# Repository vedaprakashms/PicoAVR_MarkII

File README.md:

# PicoAVR_MarkII
PicoAVR Mark II board redesigned based on CH552G, this project is heavily influenced by  https://github.com/vedaprakashms/AVR-Programmer/tree/master/picoAVR_Programmer

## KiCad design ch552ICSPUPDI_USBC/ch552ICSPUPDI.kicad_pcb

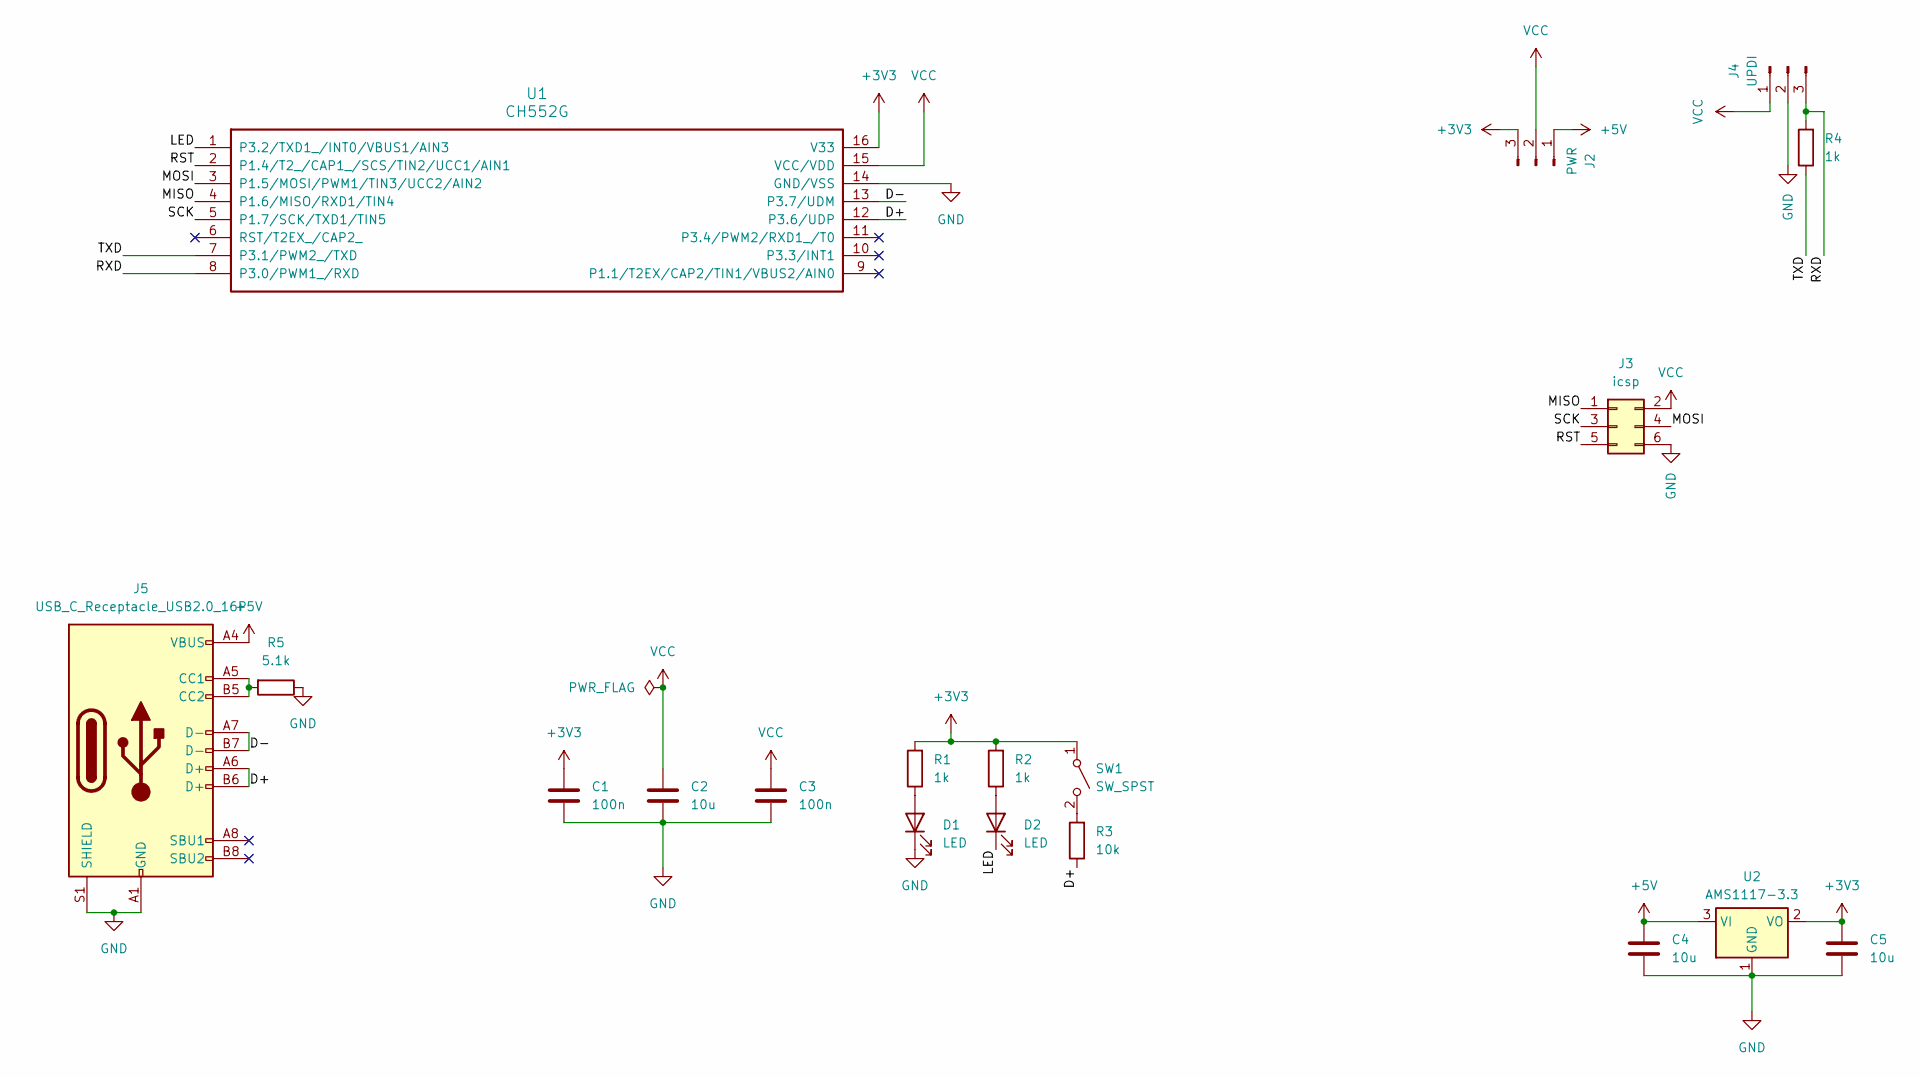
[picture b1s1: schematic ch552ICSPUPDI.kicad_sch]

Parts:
C1, C3: 100n; C_0603_1608Metric_Pad1.08x0.95mm_HandSolder
C2, C4, C5: 10u; C_1206_3216Metric_Pad1.33x1.80mm_HandSolder
D1, D2: LED; LED_0603_1608Metric_Pad1.05x0.95mm_HandSolder
J2: PWR; PinHeader_1x03_P2.54mm_Vertical
J3: icsp; PinSocket_2x03_P2.54mm_Vertical
J4: UPDI; PinHeader_1x03_P2.54mm_Vertical
J5: USB_C_Receptacle_USB2.0_16P; USB_C_Receptacle_GCT_USB4105-xx-A_16P_TopMnt_Horizontal
R1, R2, R4: 1k; R_0402_1005Metric_Pad0.72x0.64mm_HandSolder
R3: 10k; R_0805_2012Metric_Pad1.20x1.40mm_HandSolder
R5: 5.1k; R_0402_1005Metric_Pad0.72x0.64mm_HandSolder
SW1: SW_SPST; SW_SPST_B3U-1000P
U1: CH552G; STC_SOP-16_3.9x9.9mm_P1.27mm
U2: AMS1117-3.3; SOT-223-3_TabPin2

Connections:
+3V3: C1.1, C5.1, J2.3, R1.2, R2.2, SW1.1 (A), U1.16 (V33), U2.2 (VO)
+5V: C4.1, J2.1, J5.A4 (VBUS), J5.A9 (VBUS), J5.B4 (VBUS), J5.B9 (VBUS), U2.3 (VI)
/D+: J5.A6 (D+), J5.B6 (D+), R3.1, U1.12 (P3.6/UDP)
/D-: J5.A7 (D-), J5.B7 (D-), U1.13 (P3.7/UDM)
/LED: D2.1 (K), U1.1 (P3.2/TXD1_/INT0/VBUS1/AIN3)
/MISO: J3.1, U1.4 (P1.6/MISO/RXD1/TIN4)
/MOSI: J3.4, U1.3 (P1.5/MOSI/PWM1/TIN3/UCC2/AIN2)
/RST: J3.5, U1.2 (P1.4/T2_/CAP1_/SCS/TIN2/UCC1/AIN1)
/RXD: J4.3, R4.2, U1.8 (P3.0/PWM1_/RXD)
/SCK: J3.3, U1.5 (P1.7/SCK/TXD1/TIN5)
/TXD: R4.1, U1.7 (P3.1/PWM2_/TXD)
GND: C1.2, C2.2, C3.2, C4.2, C5.2, D1.1 (K), J3.6, J4.2, J5.A1 (GND), J5.A12 (GND), J5.B1 (GND), J5.B12 (GND), J5.S1 (SHIELD), R5.1, U1.14 (GND/VSS), U2.1 (GND)
unnamed: D1.2 (A), R1.1
unnamed: D2.2 (A), R2.1
unnamed: J5.A5 (CC1), J5.B5 (CC2), R5.2
unnamed: R3.2, SW1.2 (B)
VCC: C2.1, C3.1, J2.2, J3.2, J4.1, U1.15 (VCC/VDD)

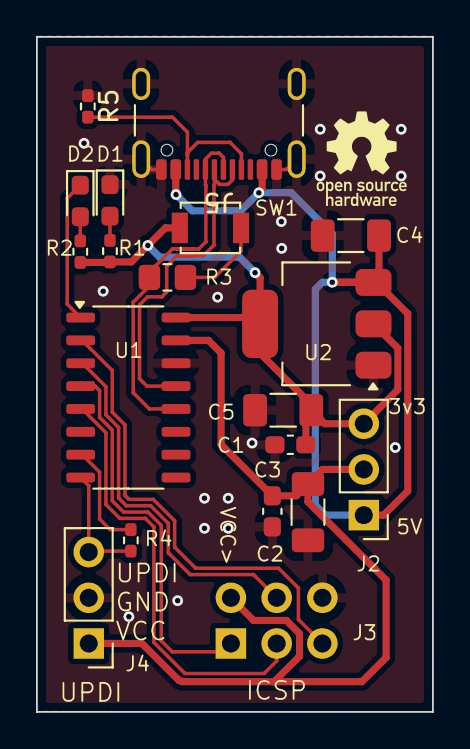
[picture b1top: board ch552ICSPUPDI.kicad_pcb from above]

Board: 2 copper layers, 22.0 x 37.5 mm, 19 parts (1 on the bottom side), 17 nets.

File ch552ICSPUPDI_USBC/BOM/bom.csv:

"Reference","Value","Datasheet","Footprint","Qty","DNP"
"C1,C3","100n","~","Capacitor_SMD:C_0603_1608Metric_Pad1.08x0.95mm_HandSolder","2",""
"C2,C4,C5","10u","~","Capacitor_SMD:C_1206_3216Metric_Pad1.33x1.80mm_HandSolder","3",""
"D1,D2","LED","~","LED_SMD:LED_0603_1608Metric_Pad1.05x0.95mm_HandSolder","2",""
"J1","USB_B_Micro","~","Connector_USB:USB_Micro-B_Molex_47346-0001","1",""
"J2","PWR","~","Connector_PinHeader_2.54mm:PinHeader_1x03_P2.54mm_Vertical","1",""
"J3","icsp","~","Connector_PinSocket_2.54mm:PinSocket_2x03_P2.54mm_Vertical","1",""
"J4","UPDI","~","Connector_PinHeader_2.54mm:PinHeader_1x03_P2.54mm_Vertical","1",""
"R1,R2,R4","1k","~","Resistor_SMD:R_0402_1005Metric_Pad0.72x0.64mm_HandSolder","3",""
"R3","10k","~","Resistor_SMD:R_0805_2012Metric_Pad1.20x1.40mm_HandSolder","1",""
"SW1","SW_SPST","~","Button_Switch_SMD:SW_SPST_B3U-1000P","1",""
"U1","CH552G","http://www.wch.cn/downloads/file/241.html","Package_SO:STC_SOP-16_3.9x9.9mm_P1.27mm","1",""
"U2","AMS1117-3.3","http://www.advanced-monolithic.com/pdf/ds1117.pdf","Package_TO_SOT_SMD:SOT-223-3_TabPin2","1",""

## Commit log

2025-04-28 hardware update
2025-04-29 update with USB C
